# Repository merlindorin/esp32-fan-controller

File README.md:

<div align="center">

# ESP32 Fan Controller

**A small KiCad board to keep my home server cabinet cool. 4 PWM fans, 4 temperature probes, one ESP32.**

</div>

## Why this exists

My home servers live in a small cabinet, hidden inside a piece of furniture I built around them. It is a credenza with a stone top, a perforated metal grille set into that top so the warm air can escape upward, and cane mesh side panels so fresh air can come in from below.

The room itself has air conditioning, but the cabinet does not. Without something actively pushing the warm air out, it just stacks up under the stone. So I needed a way to manage the airflow.

<table align="center">
  <tr>
    <td align="center">
      
    </td>
  </tr>
  <tr>
    <td align="center"><sub>The cabinet. Stone top with the perforated exhaust grille against the wall, servers behind the cane mesh panels.</sub></td>
  </tr>
</table>

I started with two breadboard prototypes (see [How I got here](#how-i-got-here)). The first one was just about understanding the temperatures: where to put the probes, where it actually gets hot. The second one was for the fans, to see how they really move the air through that perforated stone grille.

Once both questions were answered, I designed this PCB. It is a small two layer board, all through-hole so I can solder it by hand on a Sunday afternoon, around €14 in parts. It runs [ESPHome](https://esphome.io/), which means it shows up directly in Home Assistant without writing any firmware.

The board is now soldered, mounted at the back of the cabinet, and the firmware in [`firmware/fancontroller.yaml`](firmware/fancontroller.yaml) keeps the two pairs of fans (one per side of the cabinet) under thermostatic control. A short press on the on-board button toggles between auto and manual; the yellow LED reflects that state.

<table align="center">
  <tr>
    <td align="center" width="50%">
      
    </td>
    <td align="center" width="50%">
      
    </td>
  </tr>
  <tr>
    <td align="center"><sub>Fans pulling air up through the perforated stone grille, controller mounted on the right wall.</sub></td>
    <td align="center"><sub>Board mounted vertically inside the cabinet, screw terminals on top, ESP32 power LED on.</sub></td>
  </tr>
</table>

## Contents

- [Features](#features)
- [Hardware overview](#hardware-overview)
  - [ESP32 GPIO map](#esp32-gpio-map)
- [Firmware (ESPHome)](#firmware-esphome)
- [How I got here](#how-i-got-here)
- [Build one yourself](#build-one-yourself)
- [Repository layout](#repository-layout)
- [Roadmap](#roadmap)
- [Discussion](#discussion)
- [License](#license)
- [Thanks](#thanks)

## Features

- 4 independent PWM fan channels (designed around Noctua NF-A14 PWM, but any standard 4-pin PC fan works)
- 4 tachometer (RPM) inputs, open-collector, with on-board pull-ups to 3.3 V
- 4 DS18B20 1-Wire temperature probes on a shared bus (single 4.7 kΩ pull-up)
- Single 12 V external input. An on-board MP1584EN buck module generates the 5 V for the ESP32
- Per-fan PTC fuse and a TVS diode at the 12 V input, for protection
- I²C expansion header (3.3 V / GND / SDA / SCL)
- Two indicator LEDs: a green one for power (lit when the 5 V rail is up) and a yellow one for status (driven by GPIO 2)
- A small tactile button for boot / user input, shared with GPIO 0
- Everything through-hole, so it can be hand-soldered without a reflow oven
- Bare board, 155 × 85 mm, with M3 mounting holes

## Hardware overview

| Block      | Component                                                       |
|------------|-----------------------------------------------------------------|
| MCU        | ESP32 DevKitC V4 (AZDelivery, 100 % Espressif layout)           |
| Power      | External 12 V / 2 A PSU, then on-board MP1584EN buck to 5 V     |
| Fans       | 4 Noctua NF-A14 PWM, plugged into 4-pin headers                 |
| Sensors    | 4 DS18B20 waterproof probes on screw terminals                  |
| Protection | 1.5KE15A TVS on the 12 V input, 4 MF-R050 PTC fuses on the fans |
| Enclosure  | No enclosure for v1, just M3 mounting holes on the bare board   |

PCB is two-layer, 155 × 85 mm, 1.6 mm thick.

<table align="center">
  <tr>
    <td align="center" width="50%">
      
    </td>
    <td align="center" width="50%">
      
    </td>
  </tr>
  <tr>
    <td align="center"><sub>2D layout. F.Cu in red, B.Cu in blue.</sub></td>
    <td align="center"><sub>KiCad 3D render of the assembled board.</sub></td>
  </tr>
</table>

### ESP32 GPIO map

| Connector | Side  | PWM (out) | Tach (in) |
|-----------|-------|-----------|-----------|
| J3        | Right | GPIO 32   | GPIO 35   |
| J4        | Right | GPIO 33   | GPIO 34   |
| J5        | Left  | GPIO 25   | GPIO 39   |
| J6        | Left  | GPIO 26   | GPIO 36   |

| Pin     | Use                              |
|---------|----------------------------------|
| 23      | 1-Wire bus (DS18B20 probes)      |
| 21 / 22 | I²C SDA / SCL                    |
| 2       | Status LED (D3 yellow, R6 470 Ω) |
| 0       | Boot / user button (SW1)         |

The probe on J8 covers the left fans (J5 + J6), the probe on J9 covers the right ones (J3 + J4). All four DS18B20 sockets (J8–J11) sit on the same 1-Wire bus, so the assignment is by ROM address in the YAML.

## Firmware (ESPHome)

The shipped firmware is [`firmware/fancontroller.yaml`](firmware/fancontroller.yaml). It exposes, in Home Assistant:

- Two fan controls (`Left Fans`, `Right Fans`), each driving that side's two fans in lockstep, plus an individual RPM sensor per physical fan (four in total, so a single seized fan is still visible)
- Two temperature probes (`Left Temp`, `Right Temp`) with their DS18B20 ROM addresses pinned
- A single `Auto Cooling` switch and three `Number` entities (`Cooling Setpoint`, `Fans Off Below`, `Fans Full Above`)
- A `Restart` button and a `User Button` binary sensor for the on-board SW1

When `Auto Cooling` is on, each side runs the same linear ramp on its own probe:

```
T ≤ Off Below            →   0 %     (silent)
Off Below < T < Setpoint →   0 → 60 % (gentle correction)
Setpoint ≤ T < Full Above → 60 → 100 % (aggressive)
T ≥ Full Above           → 100 %     (max effort)
```

The setpoint sits inside the band on purpose, so a stable cabinet parks the fans at around 60 % instead of oscillating between full speed and off. All three thresholds are editable live from HA; defaults are 24 / 27 / 30 °C.

The on-board button toggles `Auto Cooling` on a short press, and reboots the ESP32 on a 3 s+ hold. The yellow LED follows `Auto Cooling`: on in auto, off in manual.

### Autonomous by design

The control loop runs entirely on the board, not in Home Assistant. That is deliberate. Each server already manages its own temperature through its own fans; this controller's job is to keep the enclosure itself in range, and it has to keep doing that even when nothing is around to tell it to.

Home Assistant here runs on one of my Kubernetes nodes, which lives in the very rack this board is cooling. Relying on it to cool the rack it runs in is a chicken-and-egg problem: if that node is the one overheating, HA could be the first thing to go down. So the thermostatic logic lives on the ESP32 itself. If HA is unreachable, the board keeps reading its probes and driving the fans on its own, the servers keep handling their own thermal management, and everything stays under control independently.

The result is layered, autonomous cooling instead of a central brain that could take itself down and put the other nodes at thermal risk. Home Assistant is for visibility and live tuning, not a dependency for the rack to stay cool.

<table align="center">
  <tr>
    <td align="center" width="50%">
      
    </td>
    <td align="center" width="50%">
      
    </td>
  </tr>
  <tr>
    <td align="center"><sub>Device controls: auto cooling, thresholds, per-side fan toggles.</sub></td>
    <td align="center"><sub>Sensors: per-side RPM and temperature.</sub></td>
  </tr>
</table>

The build / flash / dashboard commands are wrapped in a [`Taskfile.yml`](Taskfile.yml). With [Task](https://taskfile.dev/) installed (`brew install go-task`):

```
task               # list available tasks
task config        # validate the YAML
task upload        # compile and OTA-flash fancontroller.local
task flash-usb PORT=/dev/cu.wchusbserial8330   # first-time USB flash
task logs          # stream logs over the network
task dashboard     # local ESPHome dashboard on :6052
```

Before the first flash, copy `firmware/secrets.example.yaml` to `firmware/secrets.yaml` and fill it in (Wi-Fi, API key, OTA password). `secrets.yaml` is git-ignored.

## How I got here

Before committing to a PCB, I validated the design with two breadboard stages.

### Stage 1, temperature monitoring with Home Assistant

I started with an ESP32 **LoLin** board and **two DS18B20 probes**, flashed with [ESPHome](https://esphome.io/) and added to Home Assistant. The question for this stage was simple: what does the temperature actually do in the server cabinet? It gave me the baseline graphs that justified active cooling, and it told me where the probes should sit (intake, exhaust, ambient).

The ESPHome YAML I used is kept here for reference: [`docs/stage1-lolin32-esphome.yaml`](docs/stage1-lolin32-esphome.yaml). Shared 1-Wire bus on GPIO 4, two `dallas_temp` entries by 64-bit address.

<table align="center">
  <tr>
    <td align="center" width="50%">
      
    </td>
    <td align="center" width="50%">
      
    </td>
  </tr>
  <tr>
    <td align="center"><sub>ESP32 LoLin with two DS18B20 probes.</sub></td>
    <td align="center"><sub>Home Assistant device page, both probes live (28.7 °C and 29.8 °C).</sub></td>
  </tr>
</table>

### Stage 2, the fan bench

For the second stage, I drove a fan directly from a separate breadboard, to actually measure how the airflow influences the temperature. Fan position, speed versus Δtemperature, how fast the cabinet responds. This is where I confirmed that the Noctua NF-A14 was the right fan, validated the PWM strategy, and figured out the per-fan power budget.

<table align="center">
  <tr>
    <td align="center">
      
    </td>
  </tr>
  <tr>
    <td align="center"><sub>Fan power and airflow test on a 30 × 70 mm protoboard.</sub></td>
  </tr>
</table>

The PCB in this repository is the consolidation of both stages: 4 probes (intake, exhaust, two ambient) and 4 PWM-controlled fans on a single board instead of breadboards.

## Build one yourself

1. **Order the bare PCB.** Any fab works, I used [Aisler](https://aisler.net/). You can upload `kicad/esp32-fan-controller.kicad_pro` directly, or export gerbers first if your fab needs them.
2. **Order the parts**, around €14 excluding VAT and shipping. The quick-paste block in [`bom/ORDER.md`](bom/ORDER.md) is verified against live Farnell France stock. Paste it into Farnell's Quick Paste / Multi-Add tool. The full BOM with notes is in [`BOM.md`](BOM.md).
3. **Pre-set the MP1584EN buck module to 5.00 V before soldering it in.** Apply 12 V on its input with a bench supply, and turn the trimpot until the output reads 5.00 V.
4. **Hand-solder.** All through-hole. The order I would suggest: passives, then diodes and LEDs, then sockets and headers, then screw terminals, and finally the ESP32 socket.
5. **Power-up check.** 12 V on J1, confirm 5 V at the M1 output pin, then plug in the ESP32. Watch the polarity at J1: D1 is a 1.5KE15A TVS, so a reversed wire short-circuits the input through the diode.

<table align="center">
  <tr>
    <td align="center">
      
    </td>
  </tr>
  <tr>
    <td align="center"><sub>Mid power-up check: 12 V test leads on J1 before plugging in the ESP32.</sub></td>
  </tr>
</table>

6. **Flash [ESPHome](https://esphome.io/).** First time over USB, after that over the air:

   ```
   cp firmware/secrets.example.yaml firmware/secrets.yaml   # fill in Wi-Fi etc.
   task flash-usb PORT=/dev/cu.wchusbserial...              # initial flash
   task upload                                              # subsequent OTAs
   ```

   Details in [Firmware (ESPHome)](#firmware-esphome).

## Repository layout

```
.
├── kicad/                            # KiCad 10 project (schematic and PCB)
├── firmware/                         # ESPHome YAML for the v1 board
│   ├── fancontroller.yaml            # Shipped firmware
│   └── secrets.example.yaml          # Template for secrets.yaml (git-ignored)
├── bom/                              # BOM CSV and ordering sheets
│   └── orders/                       # Generated distributor cart CSVs
├── docs/
│   ├── images/                       # Photos, schematic renders, screenshots
│   └── stage1-lolin32-esphome.yaml   # ESPHome config used on the temperature prototype
├── BOM.md                            # Human-readable BOM with notes
├── Taskfile.yml                      # `task config / upload / logs / dashboard`
├── LICENSE                           # MIT
└── README.md
```

## Roadmap

**Next**

- [ ] Replace the missing right-side fan (J4) once the second NF-A14 arrives
- [ ] Long-term temperature graph in Grafana, to see how the auto-cooling curve actually plays out over a week

**Later**

- [ ] An actual enclosure for the PCB. The CamdenBoss CNMB/9 DIN-rail kit is a candidate, the board is already short-edge-connector friendly
- [ ] A v2 silkscreen polish, based on what I learned during assembly (polarity marks on J1, clearer pin-1 on the fan headers)

**Done**

- ✅ Schematic, ERC clean
- ✅ PCB layout, DRC clean, 0 violations, 0 unconnected
- ✅ Bare PCB ordered (Aisler)
- ✅ BOM verified against live Farnell stock
- ✅ Components ordered (Farnell)
- ✅ Board assembled and brought up on the bench
- ✅ Mounted in the cabinet, three fans and two DS18B20s live
- ✅ ESPHome config shipped: two per-side fan groups (4 PWM channels, 4 RPM sensors), 2 temp probes, thermostatic auto-cooling, button + LED status

## Discussion

Shared and discussed here:

- [r/esp32](https://www.reddit.com/r/esp32/comments/1ueic1q/esp32_fan_controller_for_my_home_server_cabinet/)
- [r/homeassistant](https://www.reddit.com/r/homeassistant/comments/1ueijpl/esphome_fan_controller_for_my_server_cabinet/)

## License

MIT, see [LICENSE](LICENSE). Hardware design files are released under the same terms, so feel free to fork, modify, fabricate and share.

## Thanks

- The KiCad team for the EDA suite
- Espressif for the ESP32 and the DevKitC reference design
- AZDelivery for an affordable ESP32 DevKitC V4 clone
- [ESPHome](https://esphome.io/), which turned the Stage 1 prototype into a one evening job
- [openotters](https://github.com/openotters/openotters), which I used as a template for this README

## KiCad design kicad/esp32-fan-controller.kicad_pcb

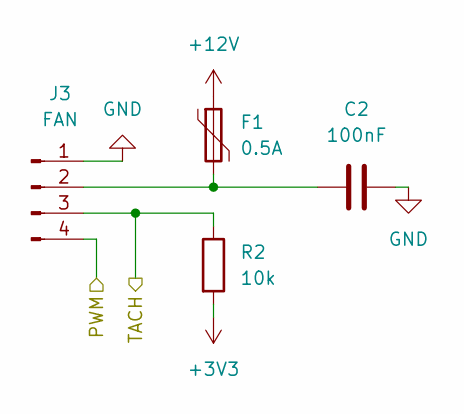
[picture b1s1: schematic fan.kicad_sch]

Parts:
C2: 100nF; C_Disc_D5.0mm_W2.5mm_P5.00mm; MPN K104K15X7RF5UH5; Farnell 2507750
F1: 0.5A; Fuse_Bourns_MF-RG300; MPN MF-R050; Farnell 9350420
J3: FAN; PinHeader_1x04_P2.54mm_Vertical; MPN 61300411121; Farnell 2356155
R2: 10k; R_Axial_DIN0207_L6.3mm_D2.5mm_P10.16mm_Horizontal; MPN CFR25J10K; Farnell 2329609

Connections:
+3V3: R2.2; also elsewhere on the board
+12V: F1.1; also elsewhere on the board
/PWM1: J3.4; also elsewhere on the board
/TACH1: J3.3, R2.1; also elsewhere on the board
GND: C2.1, J3.1; also elsewhere on the board
unnamed: C2.2, F1.2, J3.2

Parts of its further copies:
C3, C4, C5: 100nF; C_Disc_D5.0mm_W2.5mm_P5.00mm; MPN K104K15X7RF5UH5; Farnell 2507750
F2, F3, F4: 0.5A; Fuse_Bourns_MF-RG300; MPN MF-R050; Farnell 9350420
J4, J5, J6: FAN; PinHeader_1x04_P2.54mm_Vertical; MPN 61300411121; Farnell 2356155
R3, R4, R5: 10k; R_Axial_DIN0207_L6.3mm_D2.5mm_P10.16mm_Horizontal; MPN CFR25J10K; Farnell 2329609

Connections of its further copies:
+3V3: R3.2, R4.2, R5.2; also elsewhere on the board
+12V: F2.1, F3.1, F4.1; also elsewhere on the board
/PWM2: J4.4; also elsewhere on the board
/PWM3: J5.4; also elsewhere on the board
/PWM4: J6.4; also elsewhere on the board
/TACH2: J4.3, R3.1; also elsewhere on the board
/TACH3: J5.3, R4.1; also elsewhere on the board
/TACH4: J6.3, R5.1; also elsewhere on the board
GND: C3.1, C4.1, C5.1, J4.1, J5.1, J6.1; also elsewhere on the board
unnamed: C3.2, F2.2, J4.2
unnamed: C4.2, F3.2, J5.2
unnamed: C5.2, F4.2, J6.2

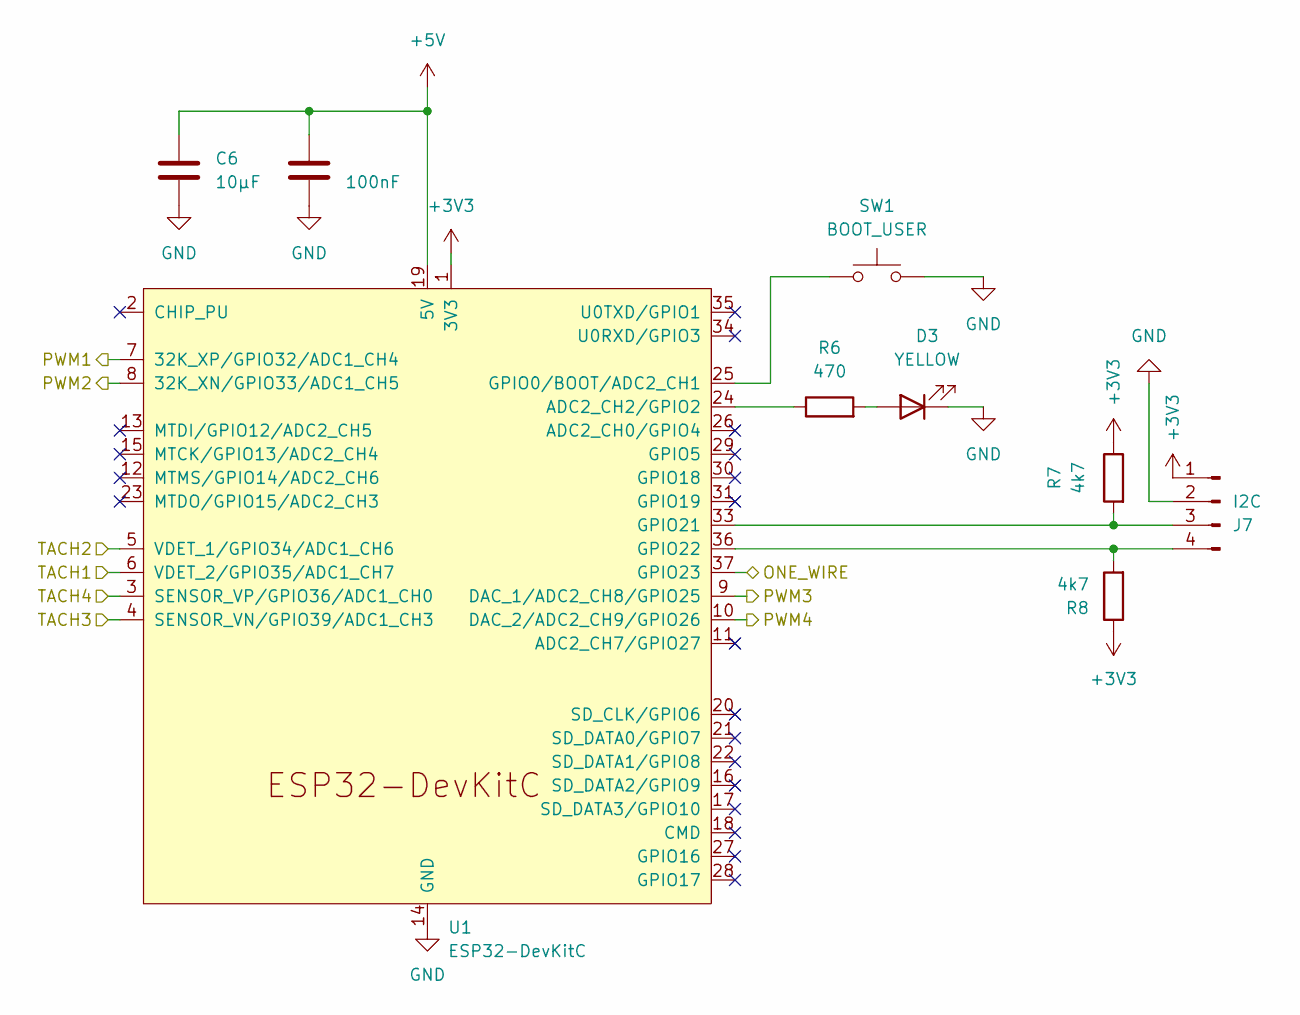
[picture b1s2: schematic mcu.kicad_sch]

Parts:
C6: 10µF; C_Disc_D7.5mm_W4.4mm_P5.00mm; MPN TAP106K016SCS; Farnell 2579016
C7: 100nF; C_Disc_D5.0mm_W2.5mm_P5.00mm; MPN K104K15X7RF5UH5; Farnell 2507750
D3: YELLOW; LED_D3.0mm; MPN TLLY4400; Farnell 1612439
J7: I2C; PinHeader_1x04_P2.54mm_Vertical; MPN 61300411121; Farnell 2356155
R6: 470; R_Axial_DIN0207_L6.3mm_D2.5mm_P10.16mm_Horizontal; MPN CFR25J470R; Farnell 2329680
R7, R8: 4k7; R_Axial_DIN0207_L6.3mm_D2.5mm_P10.16mm_Horizontal; MPN CFR25J4K7; Farnell 2329685
SW1: BOOT_USER; SW_PUSH_6mm; MPN B3F-1000; Farnell 176432
U1: ESP32-DevKitC

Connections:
+3V3: J7.1, R7.1, R8.1, U1.1 (3V3); also elsewhere on the board
+5V: C6.1, C7.1, U1.19 (5V); also elsewhere on the board
/ONE_WIRE: U1.37 (GPIO23); also elsewhere on the board
/PWM1: U1.7 (32K_XP/GPIO32/ADC1_CH4); also elsewhere on the board
/PWM2: U1.8 (32K_XN/GPIO33/ADC1_CH5); also elsewhere on the board
/PWM3: U1.9 (DAC_1/ADC2_CH8/GPIO25); also elsewhere on the board
/PWM4: U1.10 (DAC_2/ADC2_CH9/GPIO26); also elsewhere on the board
/TACH1: U1.6 (VDET_2/GPIO35/ADC1_CH7); also elsewhere on the board
/TACH2: U1.5 (VDET_1/GPIO34/ADC1_CH6); also elsewhere on the board
/TACH3: U1.4 (SENSOR_VN/GPIO39/ADC1_CH3); also elsewhere on the board
/TACH4: U1.3 (SENSOR_VP/GPIO36/ADC1_CH0); also elsewhere on the board
GND: C6.2, C7.2, D3.1 (K), J7.2, SW1.2, U1.14 (GND), U1.32 (GND), U1.38 (GND); also elsewhere on the board
unnamed: D3.2 (A), R6.2
unnamed: J7.3, R7.2, U1.33 (GPIO21)
unnamed: J7.4, R8.2, U1.36 (GPIO22)
unnamed: R6.1, U1.24 (ADC2_CH2/GPIO2)
unnamed: SW1.1, U1.25 (GPIO0/BOOT/ADC2_CH1)

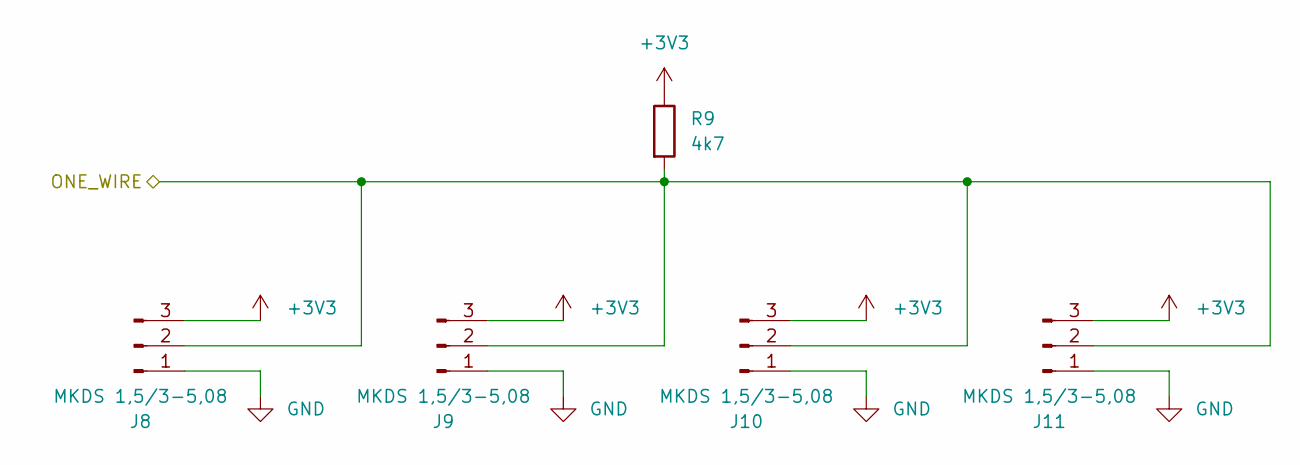
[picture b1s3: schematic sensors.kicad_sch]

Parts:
J8, J9, J10, J11: MKDS 1,5/3-5,08; TerminalBlock_Phoenix_MKDS-1,5-3-5.08_1x03_P5.08mm_Horizont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; MPN 1715734; Farnell 3041530
R9: 4k7; R_Axial_DIN0207_L6.3mm_D2.5mm_P10.16mm_Horizontal; MPN CFR25J4K7; Farnell 2329685

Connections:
+3V3: J8.3, J9.3, J10.3, J11.3, R9.1; also elsewhere on the board
/ONE_WIRE: J8.2, J9.2, J10.2, J11.2, R9.2; also elsewhere on the board
GND: J8.1, J9.1, J10.1, J11.1; also elsewhere on the board

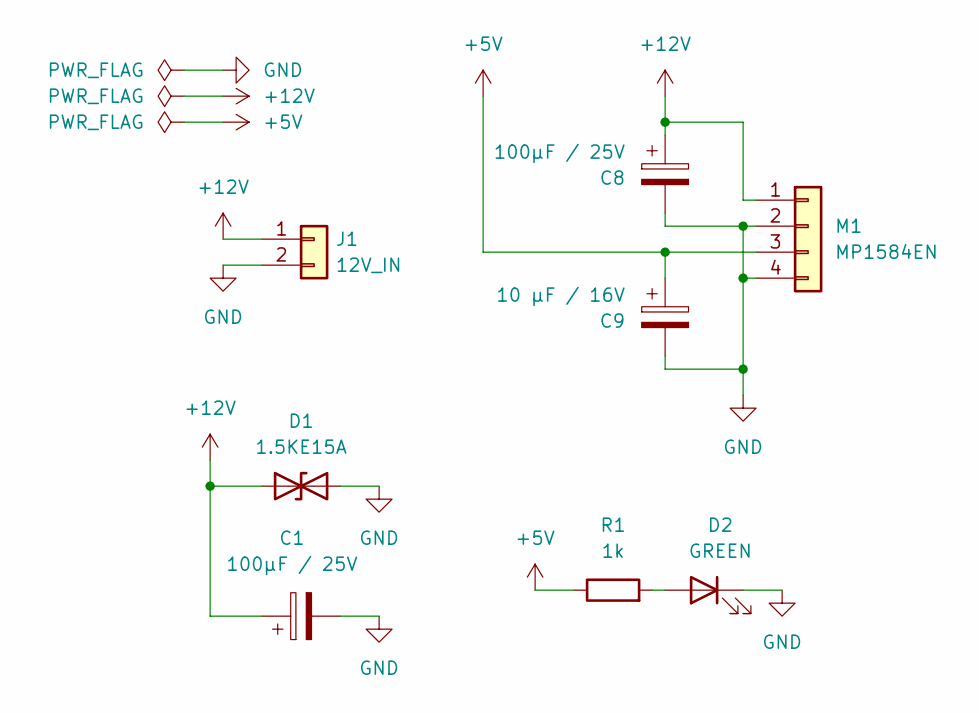
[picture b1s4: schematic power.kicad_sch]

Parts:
C1, C8: 100µF / 25V; CP_Radial_D8.0mm_P3.50mm; MPN MCGPR25V107M6.3X11; Farnell 9451188
C9: 10 µF / 16V; CP_Radial_D8.0mm_P3.50mm; MPN ECA1CHG100; Farnell 1907193
D1: 1.5KE15A; D_DO-15_P10.16mm_Horizontal; MPN 1.5KE15A; Farnell 2765092
D2: GREEN; LED_D3.0mm; MPN L-934LGD; Farnell 1142509
J1: 12V_IN; TerminalBlock_Phoenix_MKDS-1,5-2-5.08_1x02_P5.08mm_Horizont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; MPN 1715721; Farnell 3041529
M1: MP1584EN; PinHeader_1x04_P2.54mm_Vertical; MPN 61300411121; Farnell 2356155
R1: 1k; R_Axial_DIN0207_L6.3mm_D2.5mm_P10.16mm_Horizontal; MPN CFR25J1K0; Farnell 2329626

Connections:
+5V: C9.1, M1.3, R1.1; also elsewhere on the board
+12V: C1.1, C8.1, D1.1 (A1), J1.1, M1.1; also elsewhere on the board
GND: C1.2, C8.2, C9.2, D1.2 (A2), D2.1 (K), J1.2, M1.2, M1.4; also elsewhere on the board
unnamed: D2.2 (A), R1.2

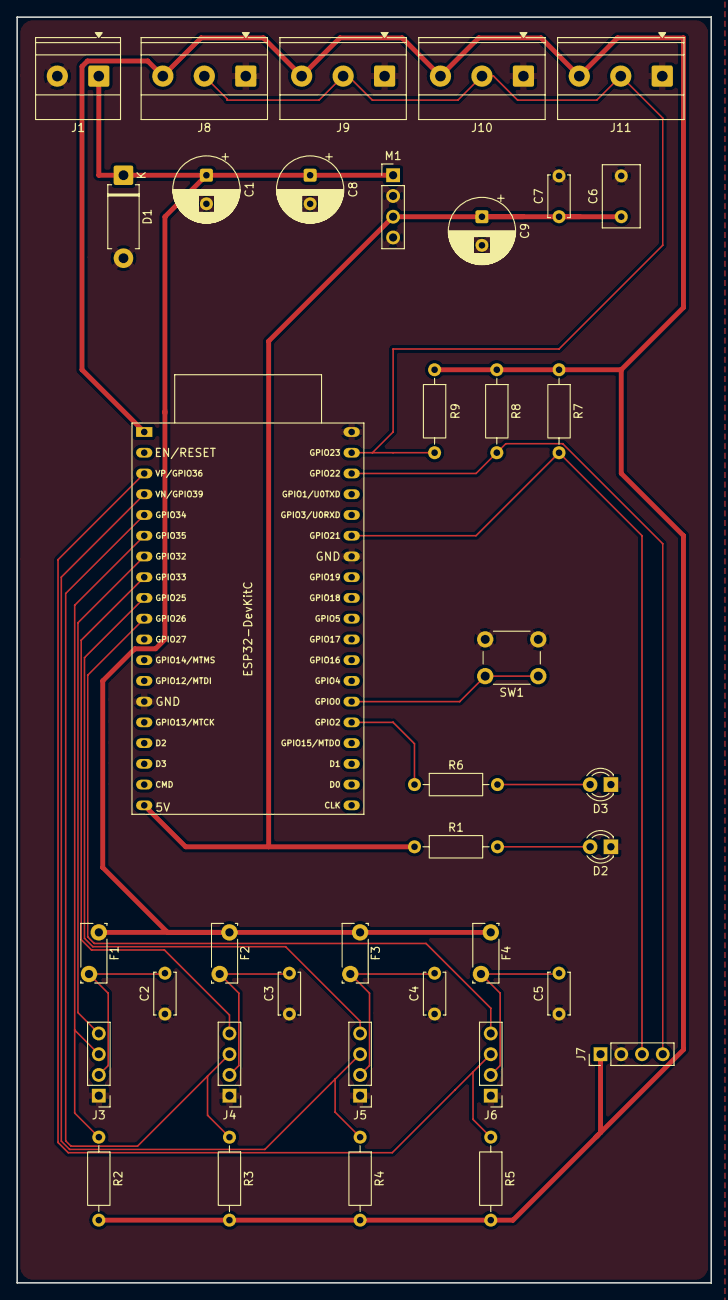
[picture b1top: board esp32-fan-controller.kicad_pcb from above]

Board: 2 copper layers, 85.0 x 155.0 mm, 38 parts (0 on the bottom side), 23 nets.

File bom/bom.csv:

Reference,Qty,Value,Footprint,MPN,Manufacturer,element14,E14_Stock,Chosen_Distributor,Datasheet,Validated,DNP,Notes
"C2(x4),C7",5,100nF,Disc_D5.0mm_W2.5mm_P5.00mm,K104K15X7RF5UH5,Vishay,2507750,,element14,,,,4x fan instances + 1 ESP32
C6,1,10µF,Disc_D7.5mm_W4.4mm_P5.00mm,TAP106K016SCS,Kyocera AVX,2579016,,,,,,
"C8,C1",2,100µF / 25V,CP_Radial_D8.0mm_P3.50mm,MCGPR25V107M6.3X11,Multicomp Pro,9451188,,element14,,,,
C9,1,10 µF / 16V,CP_Radial_D8.0mm_P3.50mm,ECA1CHG100,Panasonic,1907193,,,,,,
D1,1,1.5KE15A,DO-15_P10.16mm_Horizontal,1.5KE15A,Littelfuse,2765092,,element14,,,,
D2,1,GREEN,LED_D3.0mm,L-934LGD,Kingbright,1142509,,element14,,,,
D3,1,YELLOW,LED_D3.0mm,TLLY4400,Vishay,1612439,,element14,,,,
F1-F4,4,0.5A,Fuse_Bourns_MF-RG300,MF-R050,Bourns,9350420,,element14,,,,4x fan instances
J1,1,12V_IN,"TerminalBlock_Phoenix_MKDS-1,5-2-5.08_1x02_P5.08mm_Horizontal",1715721,Phoenix Contact,3041529,,,,,,
J3-J6,4,FAN,PinHeader_1x04_P2.54mm_Vertical,61300411121,Wurth Elektronik,2356155,,element14,,,,4x fan headers
J7,1,I2C,PinHeader_1x04_P2.54mm_Vertical,61300411121,Wurth Elektronik,2356155,,,,,,
"J10,J9,J8,J11",4,"MKDS 1,5/3-5,08","TerminalBlock_Phoenix_MKDS-1,5-3-5.08_1x03_P5.08mm_Horizontal",1715734,Phoenix Contact,3041530,,,,,,
M1,1,MP1584EN,PinHeader_1x04_P2.54mm_Vertical,61300411121,Wurth Elektronik,2356155,,,,,,
R1,1,1k,Axial_DIN0207_L6.3mm_D2.5mm_P10.16mm_Horizontal,CFR25J1K0,TE Connectivity,2329626,,,,,,
R2-R5,4,10k,Axial_DIN0207_L6.3mm_D2.5mm_P10.16mm_Horizontal,CFR25J10K,TE Connectivity,2329609,,element14,,,,4x tach pull-ups
R6,1,470,Axial_DIN0207_L6.3mm_D2.5mm_P10.16mm_Horizontal,CFR25J470R,TE Connectivity,2329680,,,,,,
"R7,R8,R9",3,4k7,Axial_DIN0207_L6.3mm_D2.5mm_P10.16mm_Horizontal,CFR25J4K7,TE Connectivity,2329685,,,,,,
SW1,1,BOOT_USER,SW_PUSH_6mm,B3F-1000,Omron,176432,,,,,,
U1,1,ESP32-DevKitC,ESP32-DevKitC,,,,,,https://docs.espressif.com/projects/esp-idf/zh_CN/latest/esp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,,,

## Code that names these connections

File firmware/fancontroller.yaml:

esphome:
  name: fancontroller
  friendly_name: Fan Controller
  on_boot:
    priority: -100
    then:
      - script.execute: sync_status

esp32:
  board: esp32dev
  framework:
    type: arduino

logger:

api:
  encryption:
    key: !secret api_encryption_key

ota:
  - platform: esphome
    password: !secret ota_password

wifi:
  ssid: !secret wifi_ssid
  password: !secret wifi_password
  ap:
    ssid: "Fan Controller Fallback"
    password: !secret fallback_password

captive_portal:

# All DS18B20 probes share GPIO23 (J8..J11 wired to the same 1-Wire bus).
one_wire:
  - platform: gpio
    pin: GPIO23

# ===== Outputs =====
output:
  # Yellow LED D3 on GPIO2 — purely an auto/manual status indicator now.
  - platform: gpio
    id: status_led_out
    pin: GPIO2
  # PWM outputs (25 kHz, Noctua spec). Each cabinet's two fans share one logical
  # channel: a template output fans the level out to both LEDC pins in lockstep.
  - platform: ledc
    id: fan_right_1_pwm
    pin: GPIO32
    frequency: 25000Hz
  - platform: ledc
    id: fan_right_2_pwm
    pin: GPIO33
    frequency: 25000Hz
  - platform: ledc
    id: fan_left_1_pwm
    pin: GPIO25
    frequency: 25000Hz
  - platform: ledc
    id: fan_left_2_pwm
    pin: GPIO26
    frequency: 25000Hz
  - platform: template
    type: float
    id: fan_right_pwm
    write_action:
      - output.set_level: { id: fan_right_1_pwm, level: !lambda return state; }
      - output.set_level: { id: fan_right_2_pwm, level: !lambda return state; }
  - platform: template
    type: float
    id: fan_left_pwm
    write_action:
      - output.set_level: { id: fan_left_1_pwm, level: !lambda return state; }
      - output.set_level: { id: fan_left_2_pwm, level: !lambda return state; }

# SW1 (BOOT_USER) on GPIO0, press-to-ground momentary.
# WARNING: GPIO0 is a strapping pin. Don't hold it at boot/reset (forces download mode).
binary_sensor:
  - platform: gpio
    name: "User Button"
    id: user_button
    pin:
      number: GPIO0
      mode:
        input: true
        pullup: true
      inverted: true
    on_click:
      # Short press: toggle Auto/Manual
      - min_length: 50ms
        max_length: 800ms
        then:
          - switch.toggle: cooling_auto
      # Long hold: reboot
      - min_length: 3s
        max_length: 10s
        then:
          - button.press: restart_button

button:
  - platform: restart
    name: "Restart"
    id: restart_button

# ===== Fans =====
# One entity per cabinet, each driving both physical fans in lockstep.
# RIGHT cabinet: J3 + J4.  LEFT cabinet: J5 + J6.
fan:
  - platform: speed
    output: fan_right_pwm
    name: "Right Fans"
    id: fan_right
  - platform: speed
    output: fan_left_pwm
    name: "Left Fans"
    id: fan_left

sensor:
  # ===== Tachometers (Noctua = 2 pulses/rev → multiply 0.5) =====
  - platform: pulse_counter
    pin: { number: GPIO35, mode: { input: true } }
    name: "Right Fan 1 RPM"
    unit_of_measurement: "RPM"
    accuracy_decimals: 0
    update_interval: 5s
    filters: [multiply: 0.5]
  - platform: pulse_counter
    pin: { number: GPIO34, mode: { input: true } }
    name: "Right Fan 2 RPM"
    unit_of_measurement: "RPM"
    accuracy_decimals: 0
    update_interval: 5s
    filters: [multiply: 0.5]
  - platform: pulse_counter
    pin: { number: GPIO39, mode: { input: true } }
    name: "Left Fan 1 RPM"
    unit_of_measurement: "RPM"
    accuracy_decimals: 0
    update_interval: 5s
    filters: [multiply: 0.5]
  - platform: pulse_counter
    pin: { number: GPIO36, mode: { input: true } }
    name: "Left Fan 2 RPM"
    unit_of_measurement: "RPM"
    accuracy_decimals: 0
    update_interval: 5s
    filters: [multiply: 0.5]

  # ===== Temperature probes =====
  - platform: dallas_temp
    name: "Left Temp"
    id: temp_left
    address: 0x72000000be310828
    update_interval: 10s
    on_value:
      then:
        - script.execute: update_left_cooling
  - platform: dallas_temp
    name: "Right Temp"
    id: temp_right
    address: 0x27000000bf5ac728
    update_interval: 10s
    on_value:
      then:
        - script.execute: update_right_cooling

# ===== Thermostatic control =====
# Left and right cabinet share one set of bounds.
# Linear ramp: off below low, full above high, 60 % at setpoint
# (setpoint sits inside the band so equilibrium parks fans at ~60 % instead of oscillating).
number:
  - platform: template
    name: "Cooling Setpoint"
    id: cooling_setpoint
    icon: mdi:thermometer
    unit_of_measurement: "°C"
    min_value: 15.0
    max_value: 50.0
    step: 0.5
    initial_value: 27.0
    restore_value: true
    optimistic: true
    mode: box
  - platform: template
    name: "Fans Off Below"
    id: cooling_low
    icon: mdi:fan-off
    unit_of_measurement: "°C"
    min_value: 10.0
    max_value: 45.0
    step: 0.5
    initial_value: 24.0
    restore_value: true
    optimistic: true
    mode: box
  - platform: template
    name: "Fans Full Above"
    id: cooling_high
    icon: mdi:fan
    unit_of_measurement: "°C"
    min_value: 15.0
    max_value: 60.0
    step: 0.5
    initial_value: 30.0
    restore_value: true
    optimistic: true
    mode: box

switch:
  - platform: template
    name: "Auto Cooling"
    id: cooling_auto
    icon: mdi:fan-auto
    optimistic: true
    restore_mode: RESTORE_DEFAULT_ON
    turn_on_action:
      - output.turn_on: status_led_out
      - script.execute: update_left_cooling
      - script.execute: update_right_cooling
    turn_off_action:
      - output.turn_off: status_led_out
      - fan.turn_off: fan_left
      - fan.turn_off: fan_right

script:
  # Align LED + cooling state to the restored auto switch on boot.
  - id: sync_status
    then:
      - lambda: |-
          if (id(cooling_auto).state) {
            id(status_led_out).turn_on();
          } else {
            id(status_led_out).turn_off();
          }
      - if:
          condition:
            switch.is_on: cooling_auto
          then:
            - script.execute: update_left_cooling
            - script.execute: update_right_cooling

  - id: update_left_cooling
    then:
      - lambda: |-
          if (!id(cooling_auto).state) return;
          if (isnan(id(temp_left).state)) return;
          float t  = id(temp_left).state;
          float lo = id(cooling_low).state;
          float sp = id(cooling_setpoint).state;
          float hi = id(cooling_high).state;
          if (lo >= sp || sp >= hi) {
            ESP_LOGW("cool-L", "Bad bounds: low=%.1f sp=%.1f high=%.1f", lo, sp, hi);
            return;
          }
          int speed;
          if (t <= lo)      speed = 0;
          else if (t < sp)  speed = (int)((t - lo) / (sp - lo) * 60.0f);
          else if (t < hi)  speed = 60 + (int)((t - sp) / (hi - sp) * 40.0f);
          else              speed = 100;
          ESP_LOGI("cool-L", "T=%.2f°C → left fans = %d%%", t, speed);
          if (speed == 0) {
            id(fan_left).turn_off().perform();
          } else {
            auto a = id(fan_left).turn_on(); a.set_speed(speed); a.perform();
          }

  - id: update_right_cooling
    then:
      - lambda: |-
          if (!id(cooling_auto).state) return;
          if (isnan(id(temp_right).state)) return;
          float t  = id(temp_right).state;
          float lo = id(cooling_low).state;
          float sp = id(cooling_setpoint).state;
          float hi = id(cooling_high).state;
          if (lo >= sp || sp >= hi) {
            ESP_LOGW("cool-R", "Bad bounds: low=%.1f sp=%.1f high=%.1f", lo, sp, hi);
            return;
          }
          int speed;
          if (t <= lo)      speed = 0;
          else if (t < sp)  speed = (int)((t - lo) / (sp - lo) * 60.0f);
          else if (t < hi)  speed = 60 + (int)((t - sp) / (hi - sp) * 40.0f);
          else              speed = 100;
          ESP_LOGI("cool-R", "T=%.2f°C → right fans = %d%%", t, speed);
          if (speed == 0) {
            id(fan_right).turn_off().perform();
          } else {
            auto a = id(fan_right).turn_on(); a.set_speed(speed); a.perform();
          }

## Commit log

2026-05-28 feat: initial release of ESP32 Fan Controller v1
    KiCad 10 design of a standalone board that controls 4 PWM fans from 4
    DS18B20 temperature probes, driven by an ESP32 DevKitC V4. Built to
    manage the airflow of a home server cabinet hidden inside a piece of
    custom furniture.
    Hardware
    - 4 PWM fan channels with tachometer feedback (Noctua NF-A14 friendly)
2026-06-14 feat(firmware): ship ESPHome config with thermostatic auto-cooling
    Adds the firmware that actually runs on the assembled board, plus the
    glue around it:
    - firmware/fancontroller.yaml: 4 fans + 2 DS18B20 probes wired by ROM,
    per-side thermostatic linear ramp driven by Left Temp / Right Temp,
    Auto Cooling switch + 3 configurable thresholds, on-board button
    toggles auto/manual on short press and reboots on 3 s hold, yellow
2026-06-24 feat(firmware): regroup fans into per-side Left/Right controls
    Collapse the four Home Assistant fan entities into two — `Left Fans`
    and `Right Fans` — each driving its side's two PWM channels in lockstep
    through a template output. The cooling scripts already ramped each side
    together, so this only changes the HA-facing entities, not the control
    behaviour.
    Per-fan tachometers are kept (four RPM sensors) so a single seized fan
2026-06-25 docs(readme): add autonomous-control rationale and Reddit discussion links
